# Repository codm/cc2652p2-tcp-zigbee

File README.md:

# cod.m ZigBee CC2652P2 TCP Coordinator
Initiated by Matthias' video to build a [ZigBee Coordinator with Ethernet connectivity](https://www.youtube.com/watch?v=Uz26JzOJVTc) we developed a small PCB to integrate everything in a small form factor - ready to go if you like.

The coordinator uses an CC2652P2 together with an [USR-K6](https://www.pusr.com/products/low-cost-ttl-to-ethernet-modules-usr-k6.html) serial ethernet gateway. The CC2652P2 is the current ZigBee implementation from Texas Intruments and supports ZigBee 3.x. The Z-Stack firmware is actively developed - much thanks to @koenkk again.

Should be usable with any Home Automation System that let's you use a TCP port instead of a local port. The module is tested with [io.broker](https://www.iobroker.net/) and [zigbee2mqtt](https://www.zigbee2mqtt.io/).

You can buy it at our webshop: https://shop.codm.de/automation/zigbee/40/zigbee-cc2652p2-tcp-ethernet-coordinator. It comes preconfigured with DHCP enabled, case and antenna.

To build a serial bridge the USR-K6 from USR IOT comes into play which implements everything needed to act as an TCP Server with a webinterface and in a small form factor.

You can find the files to 3d print the case on printables:
https://www.printables.com/de/model/179517-codm-cc2652p2-tcp-zigbee-coordiantor-case

## Configuration
If your home automation system let's you configure `TI ZStack/CCxxxx` devices as ZigBee coordinator over a TCP connection, you should be good to go. 

### io.broker
Install the zigbee adapter and configure the portname to `tcp://<ip-of-cc2652p-tcp>:20108` and choose `TI ZStack/CCxxxx` under type. After restarting the adapter everything should work. Check the logs for details like

```
Coordinator firmware version: {"type":"zStack3x0","meta":{"transportrev":2,"product":1,"majorrel":2,"mino rrel":7,"maintrel":1,"revision":20220103}}
```

### zigbee2mqtt
In `data/configuration.yaml` use the tcp connection under port in the section serial like so (including single quotes): 
```
serial: 
  port: 'tcp://<ip-of-cc2652p-tcp>:20108'
```

### USR-K6
If you factory reset the USR-K6 you'll need to configure the serial bridge again (see image). It act's as a TCP-Server on the given port.

The default IP of the USR-K6 is `192.168.0.7` and username/password for the webinterface is `admin/admin`.

## Update
You can update the Z-Stack firmware on the CC2652P2 module via network using [ZigStar's stunning ZigStar MultiTool](https://zig-star.com/radio-docs/zigstar-multi-tool/).

Find the Z-Stack Firmware in [Koenkks Z-Stack Firmware Repository]([https://github.com/Koenkk/Z-Stack-firmware/tree/master/coordinator/Z-Stack_3.x.0/bin](https://github.com/Koenkk/Z-Stack-firmware/releases)) and check the table for which file use for the __cod.m ZigBee CC2652P2 TCP Coordinator__. Usually this is `CC1352P2_CC2652P_launchpad_*.zip`.

Open up the case and bring the CC2652P2 in bootloader mode by holding FLASH, pressing RESET and then release FLASH. After that choose the settings in the MultiTool according to the screenshot and of course use the IP of _your_ CC2652P TCP Coordinator:

After that powercycle the module and use again.

Flashing via JTAG is also possible through the corresponding header.

# Thanks
* @klein0r Inital Idea - https://haus-automatisierung.com/
* @koenkk Z-Stack Firmware - https://github.com/Koenkk/Z-Stack-firmware
* @xyzroe ZigStar MultiTool - https://github.com/xyzroe/ZigStarGW-MT

# License
[CC-BY-NC-SA 4.0](https://creativecommons.org/licenses/by-nc-sa/4.0/)

[![CC BY-NC-SA 4.0][cc-by-nc-sa-image]][cc-by-nc-sa]

[cc-by-nc-sa]: http://creativecommons.org/licenses/by-nc-sa/4.0/
[cc-by-nc-sa-image]: https://licensebuttons.net/l/by-nc-sa/4.0/88x31.png

cod.m GmbH, Patrik Mayer, 2022

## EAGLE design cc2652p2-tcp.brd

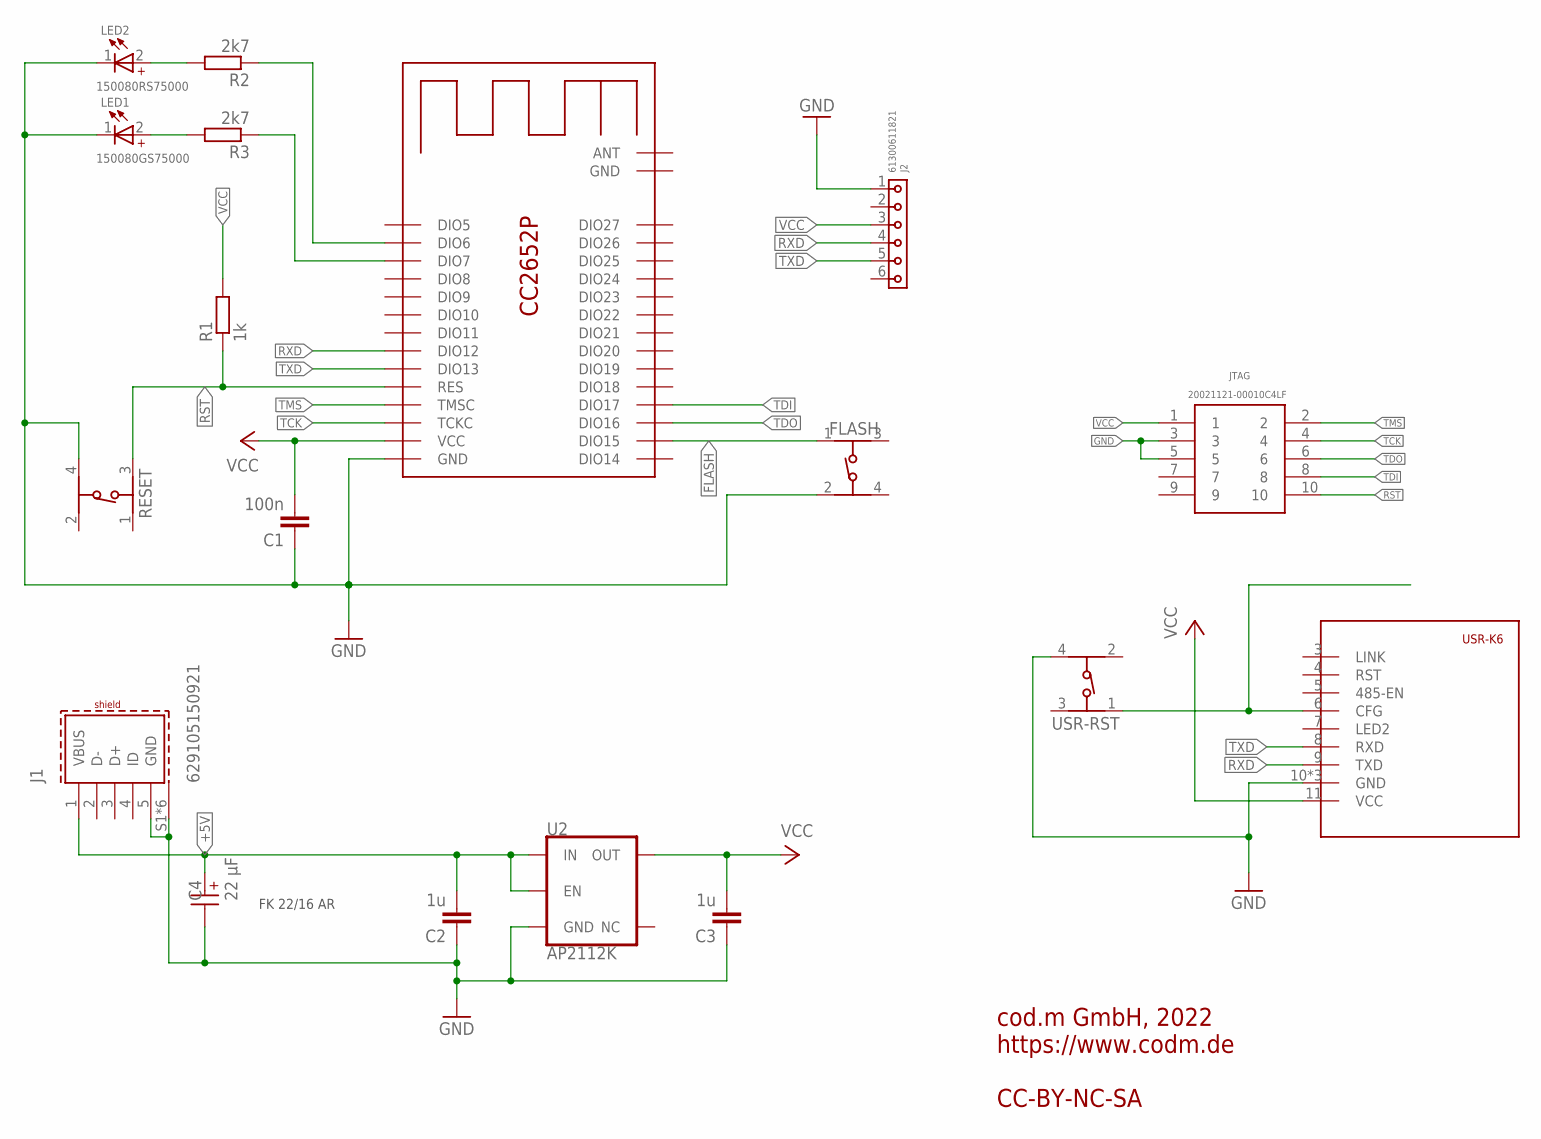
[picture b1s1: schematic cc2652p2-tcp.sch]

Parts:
C1: 100n; C0805
C2, C3: 1u; C0805
C4: 22 µF; WCAP-ASLL_5X5.5(DXL)
FLASH: 434153017835
J1: 629105150921
J2: 61300611821
JTAG: 20021121-00010C4LF; 2002112100010C4LF
LED1: 150080GS75000; WL-SMCW_0805
LED2: 150080RS75000; WL-SMCW_0805
R1: 1k; R0805
R2, R3: 2k7; R0805
RESET: 434153017835
U1: CC2652P2-DUOWEISI
U2: AP2112K; SOT23-5
U3: USR-K6
USR-RST: 434153017835

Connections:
+5V: C2.2, C4.1 (+), J1.1 (VBUS), U2.1 (IN), U2.3 (EN)
FLASH: FLASH.1, U1.DIO15
GND: C1.1, C2.1, C3.1, C4.2 (-), FLASH.2 (3), J1.5 (GND), J1.S1 (SHIELD), J1.S2 (SHIELD), J1.S3 (SHIELD), J1.S4 (SHIELD), J1.S5 (SHIELD), J1.S6 (SHIELD), J2.1, JTAG.3, JTAG.5, LED1.1 (-), LED2.1 (-), RESET.4, U1.GND, U2.2 (GND), U3.10 (GND), U3.GND@1 (GND), U3.GND@2 (GND), USR-RST.4
unnamed: U3.6 (CFG), USR-RST.1
unnamed: R3.1, U1.DIO7
unnamed: R2.1, U1.DIO6
unnamed: LED2.2 (+), R2.2
unnamed: LED1.2 (+), R3.2
RST: JTAG.10, R1.1, RESET.3 (2), U1.RES
RXD: J2.4, U1.DIO12, U3.9 (TXD)
TCK: JTAG.4, U1.TCKC
TDI: JTAG.8, U1.DIO17
TDO: JTAG.6, U1.DIO16
TMS: JTAG.2, U1.TMSC
TXD: J2.5, U1.DIO13, U3.8 (RXD)
VCC: C1.2, C3.2, J2.3, JTAG.1, R1.2, U1.VCC, U2.5 (OUT), U3.11 (VCC)

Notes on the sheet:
cod.m GmbH, 2022 https://www.codm.de CC-BY-NC-SA
FK 22/16 AR

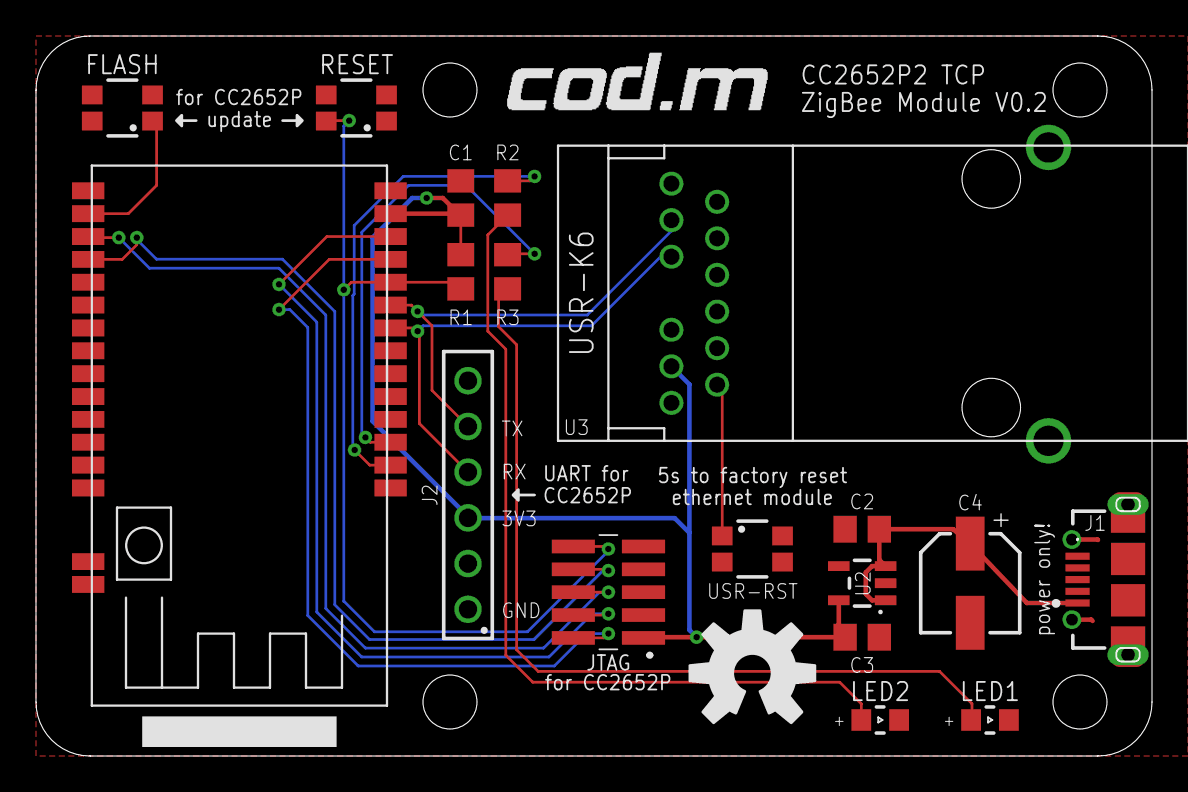
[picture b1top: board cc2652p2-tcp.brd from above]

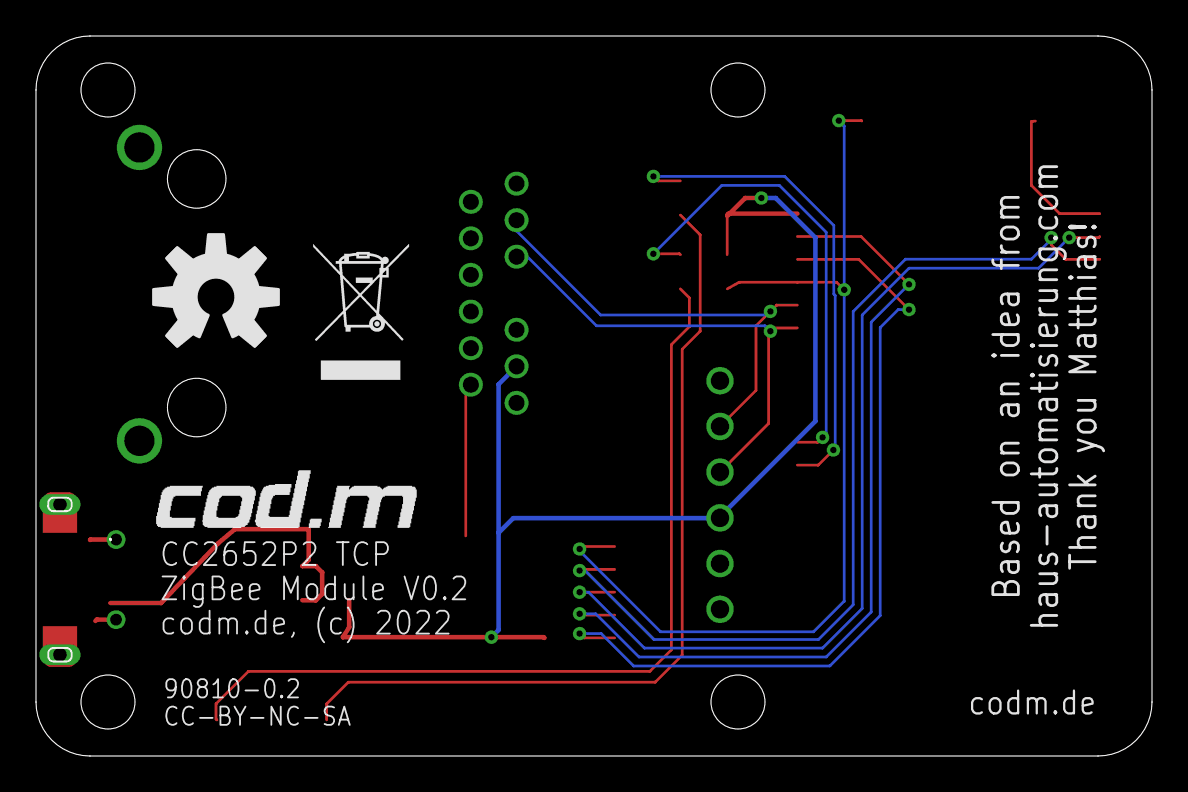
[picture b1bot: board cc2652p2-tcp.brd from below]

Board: 2 copper layers, 61.9 x 39.9 mm, 23 parts (3 on the bottom side), 16 nets.

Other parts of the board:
U$1, U$2: CODM-LOGO
U$4, U$5: OSHW-LOGO-L
U$6: WEEE-LOGO-5MM

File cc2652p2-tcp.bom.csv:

"Qty";"Value";"Device";"Package";"Parts";"Description";"APPLICATION";"CHIP-TECHNOLOGY";"DATASHEET-URL";"DESCRIPTION";"DF";"DIAMETER";"DOMINANT-WAVELENGTH";"EMITTING-COLOR";"FORWARD-VOLTAGE";"GENDER";"GERDER";"H";"HEIGHT";"I-LEAK";"I-RIPPLE";"INTERFACE-TYPE";"IR";"IR1";"L";"LUMINOUS-INTENSITY";"MANUFACTURER_NAME";"MANUFACTURER_PART_NUMBER";"MOUNT";"MOUSER_PART_NUMBER";"MOUSER_PRICE-STOCK";"OPERATING-TEMPERATURE";"OPERATION-FORCE";"PACKAGING";"PART-NUMBER";"PEAK-WAVELENGTH";"PINS";"PITCH";"POPULARITY";"PROD_ID";"QTY";"ROWS";"SPICEPREFIX";"TECHNICAL-REFERENCE";"TYPE";"VALUE";"VR";"WORKING-VOLTAGE";"Z";
"3";"";"434153017835";"434153017835";"FLASH, RESET, USR-RST";"WS-TASV J-Bend SMT Tact Switch 3.5x2.9 mm";"";"";"https://www.we-online.com/catalog/datasheet/434153017835.pdf";"";"";"";"";"";"";"";"";"1.7mm";"";"";"";"";"";"";"";"";"";"";"";"";"";"";"350g";"";"434153017835";"";"";"";"";"";" 4000 ";"";"";"";"";"";"";"";"";
"1";" 61300611821 ";"6130XX11821_61300611821";"61300611821";"J2";"WR-PHD 2.54 mm Socket Header";"";"";"https://www.we-online.com/catalog/datasheet/61300611821.pdf";"";"";"";"";"";"";"Socket Header";"";"";"";"";"";"";"3A";"";"";"";"";"";"THT";"";"";"";"";"Tray";" 61300611821 ";"";" 6 ";"2.54mm";"";"";"";"Single";"";"";"Straight";" 61300611821 ";"";"";"";
"1";"100n";"C-EUC0805";"C0805";"C1";"CAPACITOR, European symbol";"";"";"";"";"";"";"";"";"";"";"";"";"";"";"";"";"";"";"";"";"";"";"";"";"";"";"";"";"";"";"";"";"88";"";"";"";"C";"";"";"";"";"";"";
"1";"150080GS75000";"WL-SMCW_0805_150080GS75000";"WL-SMCW_0805";"LED1";"WL-SMCW SMT Mono-color Chip LED Waterclea";"";"InGaN";"https://www.we-online.com/catalog/datasheet/150080GS75000.pdf";"";"";"";"525nm";"Green";"140°";"";"";"";"";"";"";"";"";"";"";"450mcd";"";"";"";"";"";"";"";"";"150080GS75000";"515nm";"";"";"";"";"";"";"";"";"";"150080GS75000";"";"";"";
"1";"150080RS75000";"WL-SMCW_0805_150080RS75000";"WL-SMCW_0805";"LED2";"WL-SMCW SMT Mono-color Chip LED Waterclea";"";"AlInGaP";"https://www.we-online.com/catalog/datasheet/150080RS75000.pdf";"";"";"";"625nm";"Red";"140°";"";"";"";"";"";"";"";"";"";"";"150mcd";"";"";"";"";"";"";"";"";"150080RS75000";"630nm";"";"";"";"";"";"";"";"";"";"150080RS75000";"";"";"";
"3";"1k";"R-EU_R0805";"R0805";"R1, R2, R3";"RESISTOR, European symbol";"";"";"";"";"";"";"";"";"";"";"";"";"";"";"";"";"";"";"";"";"";"";"";"";"";"";"";"";"";"";"";"";"86";"";"";"";"R";"";"";"";"";"";"";
"2";"1u";"C-EUC0805";"C0805";"C2, C3";"CAPACITOR, European symbol";"";"";"";"";"";"";"";"";"";"";"";"";"";"";"";"";"";"";"";"";"";"";"";"";"";"";"";"";"";"";"";"";"88";"";"";"";"C";"";"";"";"";"";"";
"1";"20021121-00010C4LF";"20021121-00010C4LF";"2002112100010C4LF";"JTAG";"Headers & Wire Housings 1.27x1.27mm BTB, Hdr Unshrd, SMT, 10 Pos";"";"";"";"Headers & Wire Housings 1.27x1.27mm BTB, Hdr Unshrd, SMT, 10 Pos";"";"";"";"";"";"";"";"";"4.55mm";"";"";"";"";"";"";"";"Amphenol";"20021121-00010C4LF";"";"649-202112100010C4LF";"https://www.mouser.com/Search/Refine.aspx?Keyword=649-202112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";"";"";"";"";"";"";"";"";"";"";"";"";"";"";"";"";"";"";
"1";"22  µF ";"WCAP-ASLL_5X5.5_865060342002";"WCAP-ASLL_5X5.5(DXL)";"C4";"WCAP-ASLL Aluminium Electrolytic Capacitors";"";"";"https://www.we-online.com/catalog/datasheet/865060342002.pdf";"";"16%";"5mm";"";"";"";"";"";"";"";"3.52uA";"150mA";"";"";"";"5.5mm";"";"";"";"";"";"";"-55 °C up to +105 °C";"";"";" 865060342002 ";"";"";"";"";"";"";"";"";"ASEC055220M016DVCTBB000";"";"22  µF ";"16V(DC)";"";"0.8Ohm";
"1";"629105150921";"629105150921";"629105150921";"J1";"WR-COM Micro USB 2.0 Type AB Horizontal";"Micro USB 2.0";"";"https://www.we-online.com/catalog/datasheet/629105150921.pdf";"";"";"";"";"";"";"";"Receptacle";"";"";"";"";"Type AB";"";"1.8A";"";"";"";"";"SMT";"";"";"";"";"Tape and Reel";"629105150921";"";" 5 ";"";"";"";"";"";"";"";"Horizontal";"629105150921";"";"30V(AC)";"";
"1";"AP2112K";"V_REG_AP2112K-3.3V";"SOT23-5";"U2";"AP2112 - 600mA CMOS LDO Regulator w/ Enable";"";"";"";"";"";"";"";"";"";"";"";"";"";"";"";"";"";"";"";"";"";"";"";"";"";"";"";"";"";"";"";"";"";"VREG-12457";"";"";"";"";"";"3.3V";"";"";"";
"1";"CC2652P2-DUOWEISI";"CC2652P2-DUOWEISI";"CC2652P2-DUOWEISI";"U1";"";"";"";"";"";"";"";"";"";"";"";"";"";"";"";"";"";"";"";"";"";"";"";"";"";"";"";"";"";"";"";"";"";"";"";"";"";"";"";"";"";"";"";"";
"1";"USR-K6";"USR-K6";"USR-K6";"U3";"";"";"";"";"";"";"";"";"";"";"";"";"";"";"";"";"";"";"";"";"";"";"";"";"";"";"";"";"";"";"";"";"";"";"";"";"";"";"";"";"";"";"";"";

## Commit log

2022-03-14 tests with ESP-01
2022-03-14 removed ESP-01
2022-03-21 V0.2
2022-04-27 removed old csv
2022-04-27 added readme and images
2022-04-27 refined readme
2022-04-28 correction on bom
2022-05-11 Update README.md with ZHA config
    Update README.md with ZHA config
2023-04-05 added instructions for flashing via network
2023-04-05 zigstar multitool settings
2025-10-16 Update README.md
    updated z-stack download url

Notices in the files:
cc2652p2-tcp.brd:
codm.de, (c) 2022
parts and their libraries:
SparkFun-Aesthetics: Licensing: Creative Commons ShareAlike 4.0 International - https://creativecommons.org/licenses/by-sa/4.0
434153017835_Eagle_WS-TASV_rev20a: Copyright: Würth Elektronik
